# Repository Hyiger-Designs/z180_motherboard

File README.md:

# All SMD Based Z180 motherboard

Based on Steve Cousin's SC126: [SC126 – Z180 MOTHERBOARD (RC2014)](https://smallcomputercentral.wordpress.com/sc126-z180-motherboard-rc2014/)

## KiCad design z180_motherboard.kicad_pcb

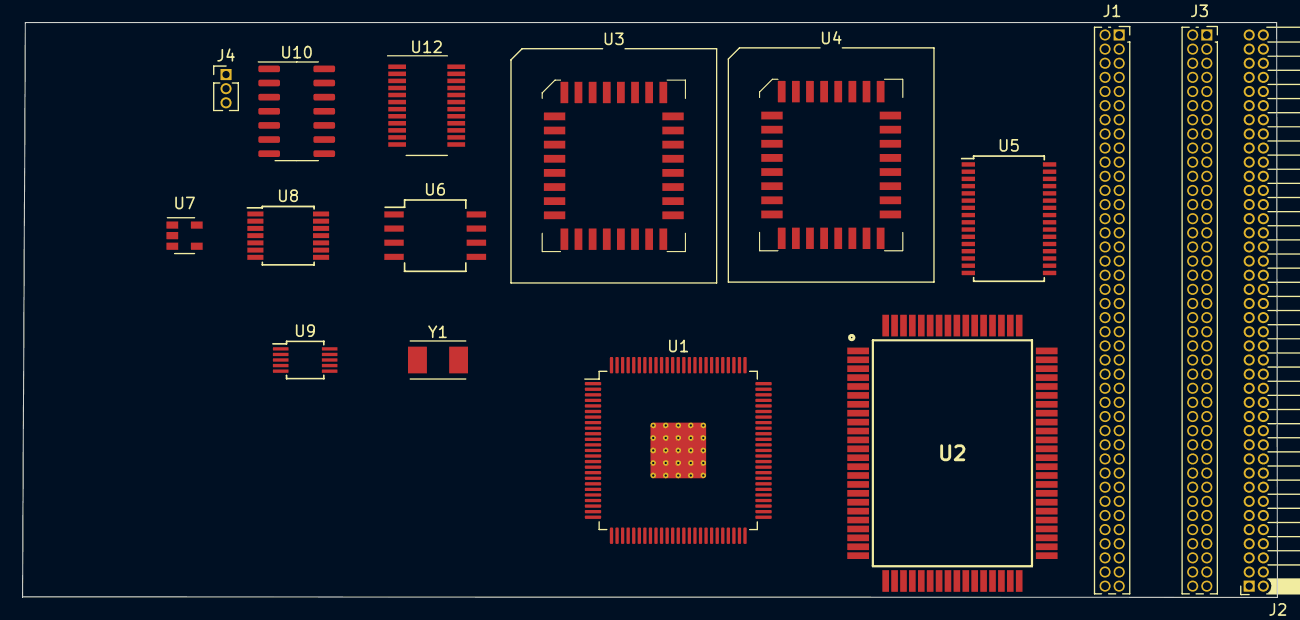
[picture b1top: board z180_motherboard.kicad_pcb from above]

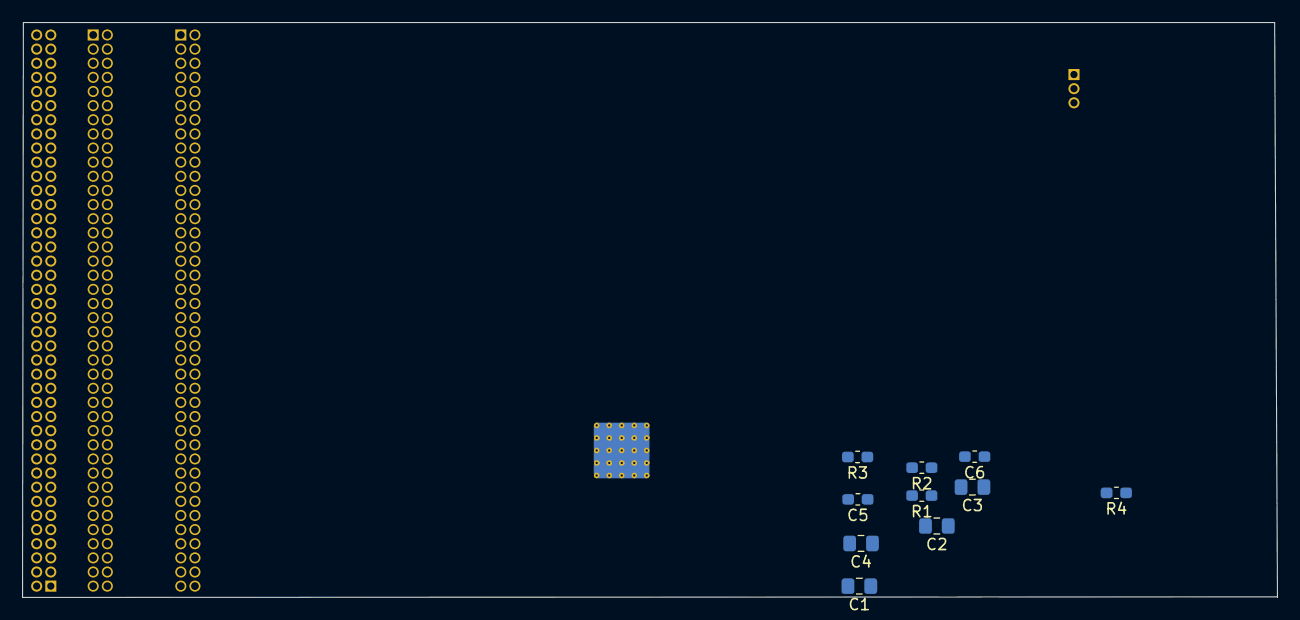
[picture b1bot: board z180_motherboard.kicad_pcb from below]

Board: 2 copper layers, 112.8 x 51.7 mm, 26 parts (10 on the bottom side), 15 nets, no tracks yet.

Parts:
C1: 22uF; C_0805_2012Metric_Pad1.15x1.40mm_HandSolder
C2: 10uF; C_0805_2012Metric_Pad1.15x1.40mm_HandSolder
C3, C4: 100nF; C_0805_2012Metric_Pad1.15x1.40mm_HandSolder
C5, C6: 0.47uF; C_0603_1608Metric_Pad1.05x0.95mm_HandSolder
J1, J3: Conn_02x40_Counter_Clockwise; PinSocket_2x40_P1.27mm_Vertical
J2: Conn_02x40_Counter_Clockwise; PinSocket_2x40_P1.27mm_Horizontal
J4: UPDI TTL; PinHeader_1x03_P1.27mm_Vertical
R1, R2: 1K; R_0603_1608Metric_Pad1.05x0.95mm_HandSolder
R3: 4K7; R_0603_1608Metric_Pad1.05x0.95mm_HandSolder
R4: 9.53K; R_0603_1608Metric_Pad1.05x0.95mm_HandSolder
U1: EPM7064STC200; TQFP-100-1EP_14x14mm_P0.5mm_EP5x5mm_ThermalVias
U2: Z8S18033FSC; QFP80P1792X2392X310-80N
U3, U4: SST39SF040; PLCC-32_SMD-Socket
U5: AS6C4008-55PCN; TSSOP-32_6.1x11mm_P0.65mm
U6: DS1302S+; SO-8_5.3x6.2mm_P1.27mm
U7: TPS7A0533PDBVR; SOT-23-5
U8: 74HC04; TSSOP-14_4.4x5mm_P0.65mm
U9: Si5351A-B-GT; MSOP-10_3x3mm_P0.5mm
U10: ATtiny1614-SS; SOIC-14_3.9x8.7mm_P1.27mm
U12: AS1115-BSST; QSOP-24_3.9x8.7mm_P0.635mm
Y1: 25MHZ 8PF; Crystal_SMD_TXC_7A-2Pin_5x3.2mm

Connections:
+3V3: C1.1, C3.1, C4.1, C5.1, C6.1, R1.1, R2.1, R4.1, U7.5, U9.1, U9.7, U10.1, U12.19
+5V: C2.1, C3.2, C4.2, U7.1, U7.3, U8.14
/IRQ: U10.6, U12.24
/SCL: R1.2, U9.4, U10.9, U12.14
/SDA: R2.2, U9.5, U10.8, U12.1
/Sheet5D3BF5C8/RX: J4.3, R3.2, U10.10
/Sheet5D3BF5C8/TX: J4.2, R3.1
GND: C1.2, C2.2, C5.2, C6.2, J4.1, U3.16, U4.16, U7.2, U8.7, U8.13, U9.8, U10.14, U12.6
unnamed: R4.2, U12.13
unnamed: U8.1, U9.10
unnamed: U8.3, U9.9
unnamed: U8.5, U9.6
unnamed: U9.2, Y1.1
unnamed: U9.3, Y1.2
VCC: U3.32, U4.32

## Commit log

2019-07-17 initial version
2019-07-18 added more chips
2019-07-18 removed rescue and cache from .gitignore
2019-07-29 rewired to fit on 50mil grid
2020-04-08 Upgraded to 6.0 alpha
